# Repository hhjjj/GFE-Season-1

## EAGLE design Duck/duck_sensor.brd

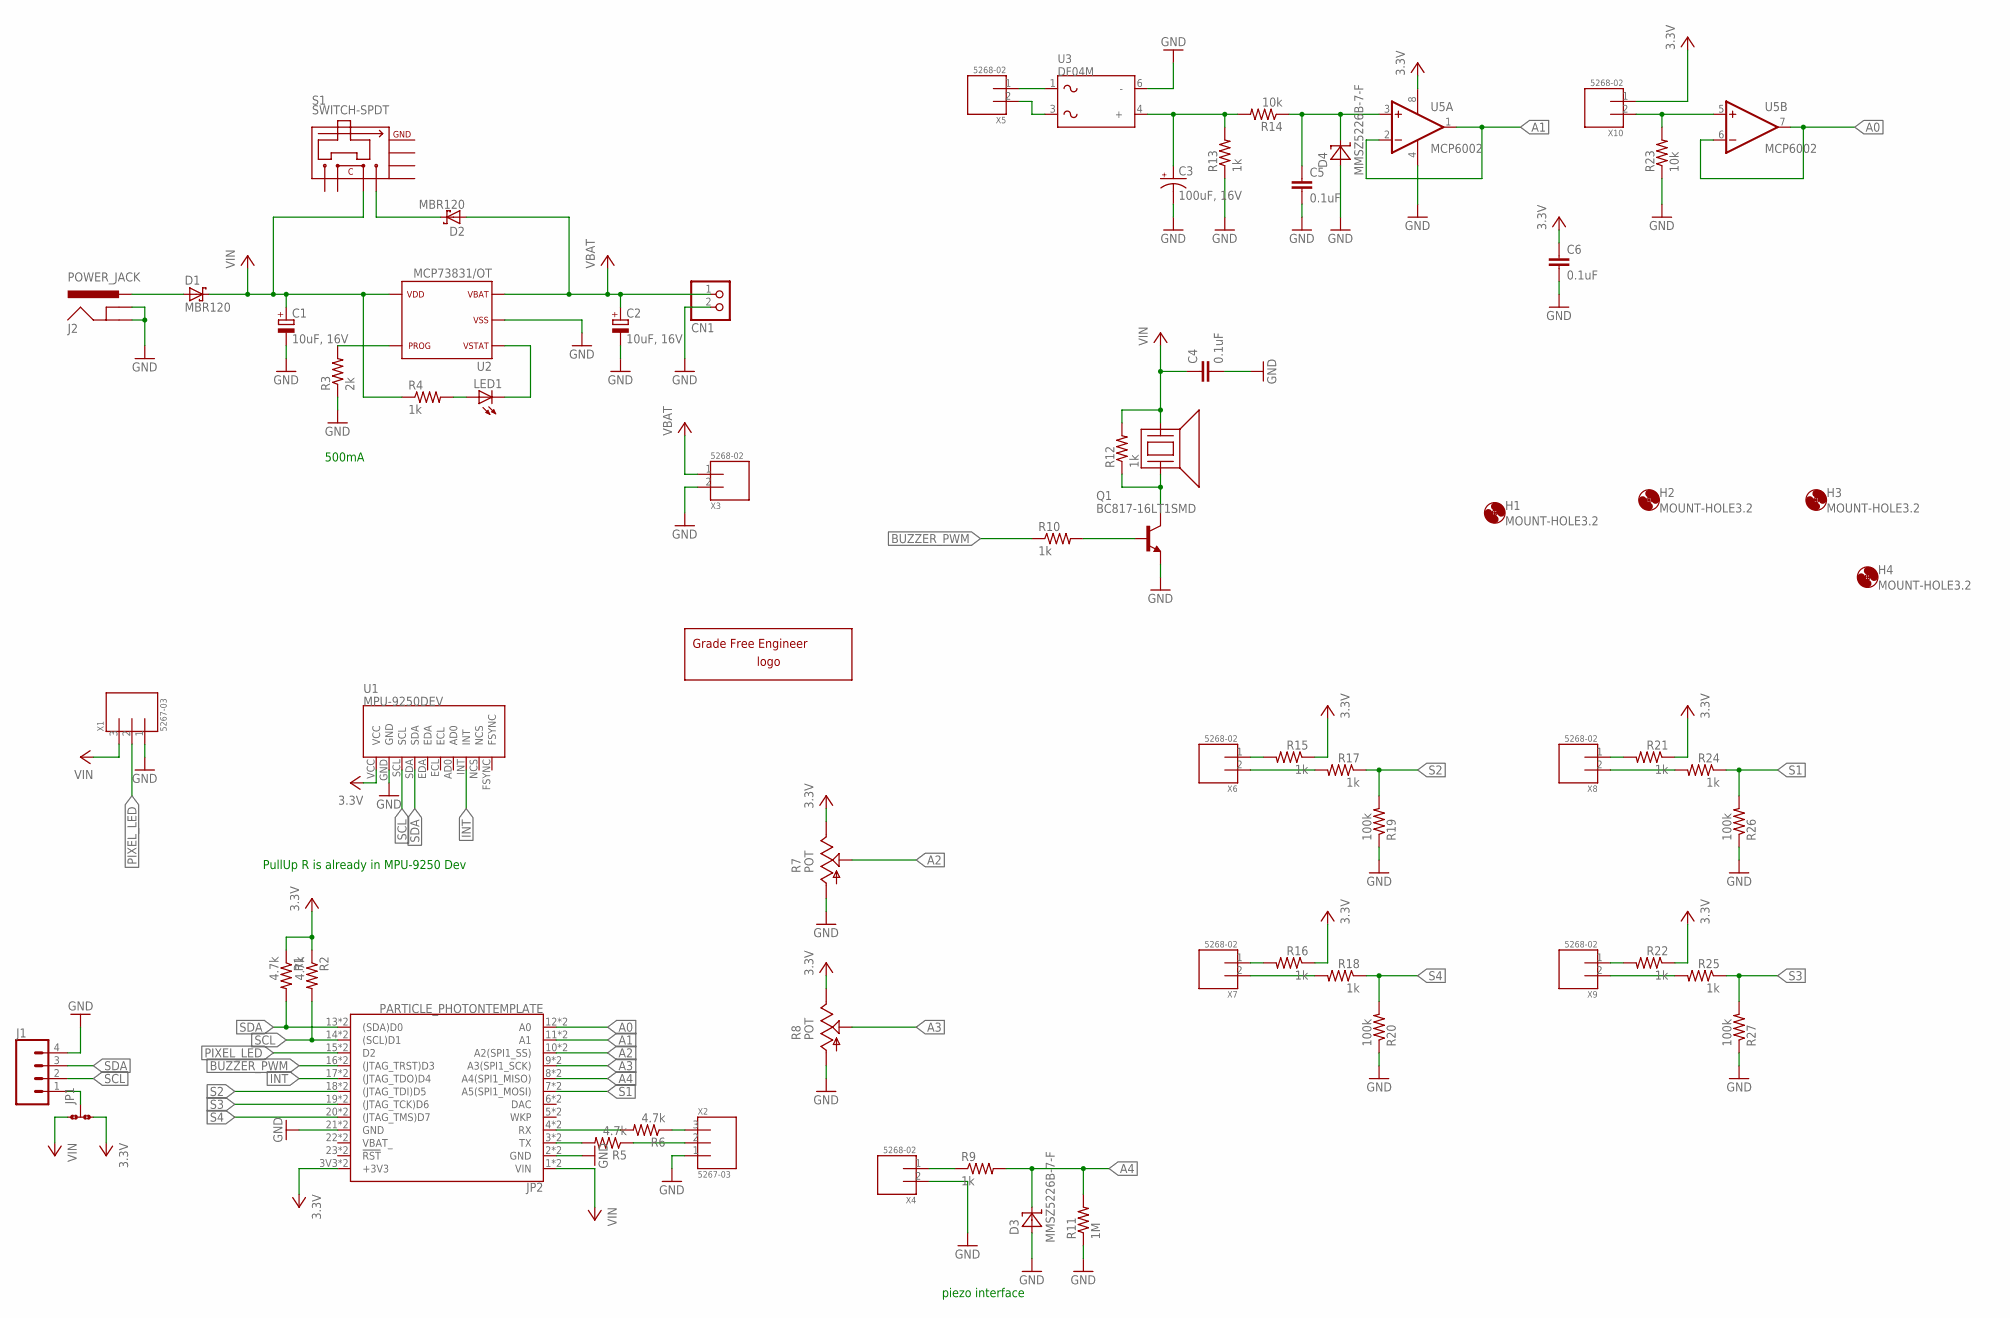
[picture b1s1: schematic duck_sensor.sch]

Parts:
C1, C2: 10uF, 16V; C1206(3216)-A
C3: 100uF, 16V; E2,5-6E
C4, C5, C6: 0.1uF; C0603(1608)_HANDSOLDER
CN1: JST_2PIN-SMT-RA; JST-PH-2-SMT-RA
D1, D2: MBR120; SOD-123
D3, D4: MMSZ5226B-7-F; SOD-123
H1, H2, H3, H4: MOUNT-HOLE3.2; 3,2
J1: CONN_04; 1X04
J2: POWER_JACK; POWER_JACK_PTH
JP1: JP2; JP2SMD0603
JP2: PARTICLE_PHOTONTEMPLATE; PARTICLE_PHOTON_TEMPLATE
LED1: LED0603; LED-0603
LOGO1: GRADEFREELOGO-20
Q1: BC817-16LT1SMD; SOT23-BEC
R1, R2, R5, R6: 4.7k; R0603(1608)_HANDSOLDER
R3: 2k; R0603(1608)_HANDSOLDER
R4, R9, R10, R12, R13, R15, R16, R17, R18, R21, R22, R24, R25: 1k; R0603(1608)_HANDSOLDER
R7, R8: POT; RK09L
R11: 1M; R0603(1608)_HANDSOLDER
R14, R23: 10k; R0603(1608)_HANDSOLDER
R19, R20, R26, R27: 100k; R0603(1608)_HANDSOLDER
S1: SWITCH-SPDT; SSSS810201
U1: MPU-9250DEV; MPU-9250
U2: MCP73831/OT; SOT23-5L
U3: DF04M; DIL06
U4: BUZZER; PS1240
U5: MCP6002; DIL08
X1, X2: 5267-03
X3, X4, X5, X6, X7, X8, X9, X10: 5268-02; 5628-02

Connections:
3.3V: C6.1, JP1.3, JP2.3V3 (+3V3), JP2.24 (+3V3), R1.1, R2.1, R7.1 (E), R8.1 (E), R15.1, R16.1, R21.1, R22.1, U1.VCC, U5.8 (V+), X10.1
A0: JP2.12 (A0), JP2.A0, U5.6 (-IN), U5.7 (OUT)
A1: JP2.11 (A1), JP2.A1, U5.1 (OUT), U5.2 (-IN)
A2: JP2.10 (A2(SPI1_SS)), JP2.A2 (A2(SPI1_SS)), R7.2 (S)
A3: JP2.9 (A3(SPI1_SCK)), JP2.A3 (A3(SPI1_SCK)), R8.2 (S)
A4: D3.C, JP2.8 (A4(SPI1_MISO)), JP2.A4 (A4(SPI1_MISO)), R9.2, R11.2
BUZZER_PWM: JP2.16 ((JTAG_TRST)D3), JP2.D3 ((JTAG_TRST)D3), R10.1
GND: C1.2 (-), C2.2 (-), C3.-, C4.2, C5.2, C6.2, CN1.2 (1), D3.A, D4.A, J1.4, J2.GND, J2.GNDBREAK, JP2.2 (GND), JP2.21 (GND), JP2.GND@0 (GND), JP2.GND@2 (GND), Q1.E, R3.1, R7.3 (A), R8.3 (A), R11.1, R13.1, R19.1, R20.1, R23.1, R26.1, R27.1, U1.GND, U2.2 (VSS), U3.6 (-), U5.4 (V-), X1.1, X2.1, X3.2, X4.2
INT: JP2.17 ((JTAG_TDO)D4), JP2.D4 ((JTAG_TDO)D4), U1.INT
unnamed: D2.C, S1.1
unnamed: R15.2, X6.1
unnamed: LED1.A, R4.2
unnamed: LED1.C, U2.1 (STAT)
unnamed: R3.2, U2.5 (PROG)
unnamed: D1.A, J2.PWR
unnamed: R9.1, X4.1
unnamed: R17.2, X6.2
unnamed: R16.2, X7.1
unnamed: R18.2, X7.2
unnamed: JP2.3 (TX), JP2.TX, R5.2
unnamed: JP2.4 (RX), JP2.RX, R6.2
unnamed: R6.1, X2.3
unnamed: R5.1, X2.2
unnamed: Q1.B, R10.2
unnamed: Q1.C, R12.1, U4.2
unnamed: J1.1, JP1.2
unnamed: C5.1, D4.C, R14.1, U5.3 (+IN)
unnamed: R23.2, U5.5 (+IN), X10.2
unnamed: R21.2, X8.1
unnamed: R24.2, X8.2
unnamed: R22.2, X9.1
unnamed: C3.+, R13.2, R14.2, U3.4 (+)
unnamed: U3.1, X5.1
unnamed: U3.3, X5.2
unnamed: R25.2, X9.2
PIXEL_LED: JP2.15 (D2), JP2.D2, X1.2
S1: JP2.7 (A5(SPI1_MOSI)), JP2.A5 (A5(SPI1_MOSI)), R24.1, R26.2
S2: JP2.18 ((JTAG_TDI)D5), JP2.D5 ((JTAG_TDI)D5), R17.1, R19.2
S3: JP2.19 ((JTAG_TCK)D6), JP2.D6 ((JTAG_TCK)D6), R25.1, R27.2
S4: JP2.20 ((JTAG_TMS)D7), JP2.D7 ((JTAG_TMS)D7), R18.1, R20.2
SCL: J1.2, JP2.14 ((SCL)D1), JP2.D1 ((SCL)D1), R2.2, U1.SCL
SDA: J1.3, JP2.13 ((SDA)D0), JP2.D0 ((SDA)D0), R1.2, U1.SDA
VBAT: C2.1 (+), CN1.1 (2), D2.A, U2.3 (VBAT), X3.1
VBAT_: JP2.22 (VBAT_), JP2.VBAT_
VIN: C1.1 (+), C4.1, D1.C, JP1.1, JP2.1 (VIN), JP2.VIN, R4.1, R12.2, S1.2, U2.4 (VDD), U4.1, X1.3

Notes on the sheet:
500mA
PullUp R is already in MPU-9250 Dev
piezo interface

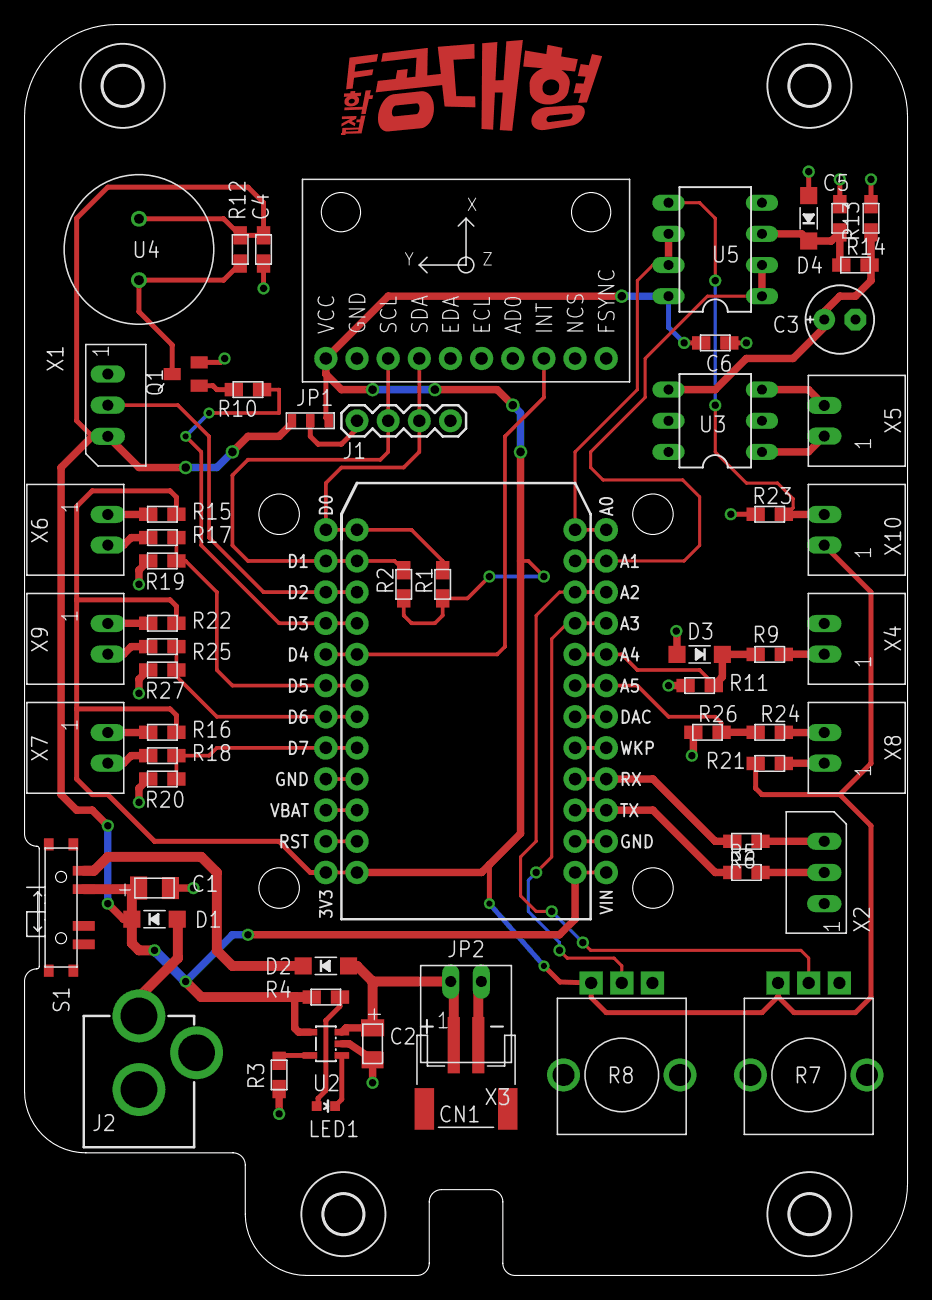
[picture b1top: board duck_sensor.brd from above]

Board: 2 copper layers, 72.0 x 102.0 mm, 65 parts (0 on the bottom side), 45 nets.

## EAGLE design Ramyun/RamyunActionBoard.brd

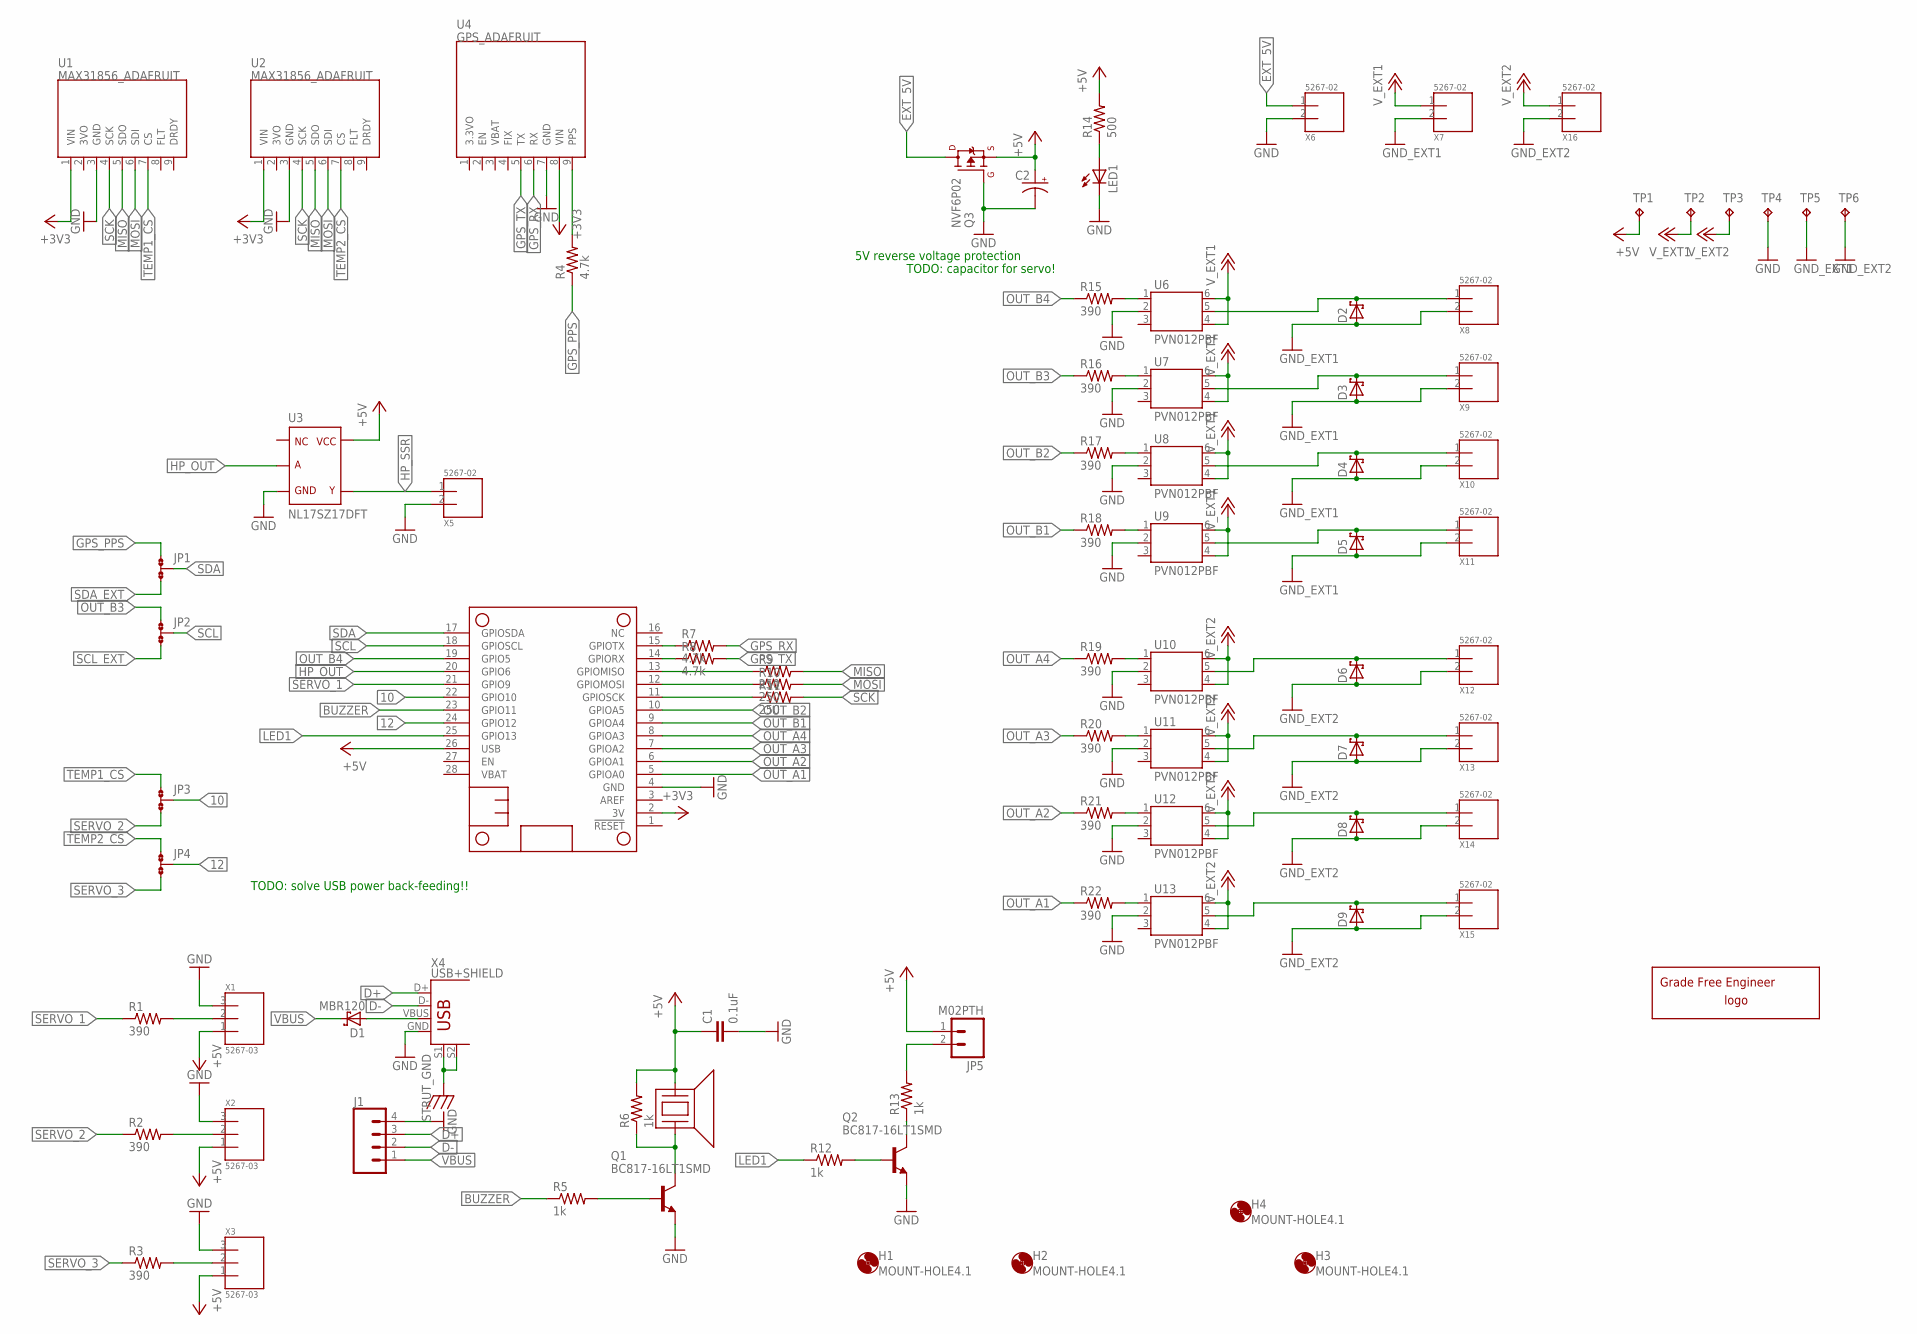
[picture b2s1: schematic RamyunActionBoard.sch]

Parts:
C1: 0.1uF; C0603(1608)_HANDSOLDER
C2: CPOL-USE3.5-8; E3,5-8
D1: MBR120; SOD-123
D2, D3, D4, D5, D6, D7, D8, D9: MBR5200VPTR-E1_V; DO-27-VERTICAL
H1, H2, H3, H4: MOUNT-HOLE4.1; 4,1
J1: CONN_04; 1X04
JP1, JP2, JP3, JP4: JP2; JP2SMD0603
JP5: M02PTH; 1X02
LED1: LED3MM
LOGO1: GRADEFREELOGO-20
MS1: FEATHERWING_NODIM; FEATHERWING_DIM
Q1, Q2: BC817-16LT1SMD; SOT23-BEC
Q3: NVF6P02; SOT223
R1, R2, R3, R15, R16, R17, R18, R19, R20, R21, R22: 390; R0603(1608)_HANDSOLDER
R4, R7, R8: 4.7k; R0603(1608)_HANDSOLDER
R5, R6, R12, R13: 1k; R0603(1608)_HANDSOLDER
R9, R10, R11: 250; R0603(1608)_HANDSOLDER
R14: 500; R0603(1608)_HANDSOLDER
TP1, TP2, TP3, TP4, TP5, TP6: TP-5010
U1, U2: MAX31856_ADAFRUIT
U3: NL17SZ17DFT; SOT-353
U4: GPS_ADAFRUIT
U5: BUZZER; PS1240
U6, U7, U8, U9, U10, U11, U12, U13: PVN012PBF; DIL06
X1, X2, X3: 5267-03
X4: USB+SHIELD; USB-B-PTH
X5, X6, X7, X8, X9, X10, X11, X12, X13, X14, X15, X16: 5267-02

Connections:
10: JP3.2, MS1.22 (GPIO10)
12: JP4.2, MS1.24 (GPIO12)
+3V3: MS1.2 (3V), U1.1 (VIN), U2.1 (VIN), U4.8 (VIN)
+5V: C1.1, C2.+, JP5.1, MS1.26 (USB), Q3.3 (S), R6.2, R14.2, TP1.TP, U3.5, U5.1, X1.1, X2.1, X3.1
BUZZER: MS1.23 (GPIO11), R5.1
D+: J1.3, X4.D+
D-: J1.2, X4.D-
EXT_5V: Q3.2 (D), Q3.4 (D), X6.1
GND: C1.2, C2.-, J1.4, LED1.K (C), MS1.4 (GND), Q1.E, Q2.E, Q3.1 (G), TP4.TP, U1.3 (GND), U2.3 (GND), U3.3, U4.7 (GND), U6.2, U7.2, U8.2, U9.2, U10.2, U11.2, U12.2, U13.2, X1.3, X2.3, X3.3, X4.GND, X5.2, X6.2
GND_EXT1: D2.A, D3.A, D4.A, D5.A, TP5.TP, X7.2, X8.2, X9.2, X10.2, X11.2
GND_EXT2: D6.A, D7.A, D8.A, D9.A, TP6.TP, X12.2, X13.2, X14.2, X15.2, X16.2
GPS_PPS: JP1.1, R4.1
GPS_RX: R7.2, U4.6 (RX)
GPS_TX: R8.2, U4.5 (TX)
HP_OUT: MS1.20 (GPIO6), U3.2
HP_SSR: U3.4, X5.1
LED1: MS1.25 (GPIO13), R12.1
MISO: R9.2, U1.5 (SDO), U2.5 (SDO)
MOSI: R10.2, U1.6 (SDI), U2.6 (SDI)
unnamed: R22.2, U13.1
unnamed: R21.2, U12.1
unnamed: R20.2, U11.1
unnamed: R19.2, U10.1
unnamed: R18.2, U9.1
unnamed: R17.2, U8.1
unnamed: R16.2, U7.1
unnamed: R15.2, U6.1
unnamed: R1.2, X1.2
unnamed: R2.2, X2.2
unnamed: R3.2, X3.2
unnamed: D1.A, X4.VBUS
unnamed: JP5.2, R13.2
unnamed: Q2.C, R13.1
unnamed: Q2.B, R12.2
unnamed: LED1.A, R14.1
unnamed: Q1.B, R5.2
unnamed: Q1.C, R6.1, U5.2
unnamed: MS1.15 (GPIOTX), R7.1
unnamed: MS1.14 (GPIORX), R8.1
unnamed: MS1.13 (GPIOMISO), R9.1
unnamed: MS1.12 (GPIOMOSI), R10.1
unnamed: D2.C, U6.5, X8.1
unnamed: D3.C, U7.5, X9.1
unnamed: D4.C, U8.5, X10.1
unnamed: D5.C, U9.5, X11.1
unnamed: D6.C, U10.5, X12.1
unnamed: D7.C, U11.5, X13.1
unnamed: D8.C, U12.5, X14.1
unnamed: D9.C, U13.5, X15.1
unnamed: MS1.11 (GPIOSCK), R11.1
unnamed: R4.2, U4.9 (PPS)
OUT_A1: MS1.5 (GPIOA0), R22.1
OUT_A2: MS1.6 (GPIOA1), R21.1
OUT_A3: MS1.7 (GPIOA2), R20.1
OUT_A4: MS1.8 (GPIOA3), R19.1
OUT_B1: MS1.9 (GPIOA4), R18.1
OUT_B2: MS1.10 (GPIOA5), R17.1
OUT_B3: JP2.1, R16.1
OUT_B4: MS1.19 (GPIO5), R15.1
SCK: R11.2, U1.4 (SCK), U2.4 (SCK)
SCL: JP2.2, MS1.18 (GPIOSCL)
SCL_EXT: JP2.3
SDA: JP1.2, MS1.17 (GPIOSDA)
SDA_EXT: JP1.3
SERVO_1: MS1.21 (GPIO9), R1.1
SERVO_2: JP3.3, R2.1
SERVO_3: JP4.3, R3.1
STRUT_GND: X4.S1, X4.S2
TEMP1_CS: JP3.1, U1.7 (CS)
TEMP2_CS: JP4.1, U2.7 (CS)
VBUS: D1.C, J1.1
V_EXT1: TP2.TP, U6.4, U6.6, U7.4, U7.6, U8.4, U8.6, U9.4, U9.6, X7.1
V_EXT2: TP3.TP, U10.4, U10.6, U11.4, U11.6, U12.4, U12.6, U13.4, U13.6, X16.1

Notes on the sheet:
TODO: capacitor for servo!
5V reverse voltage protection
TODO: solve USB power back-feeding!!

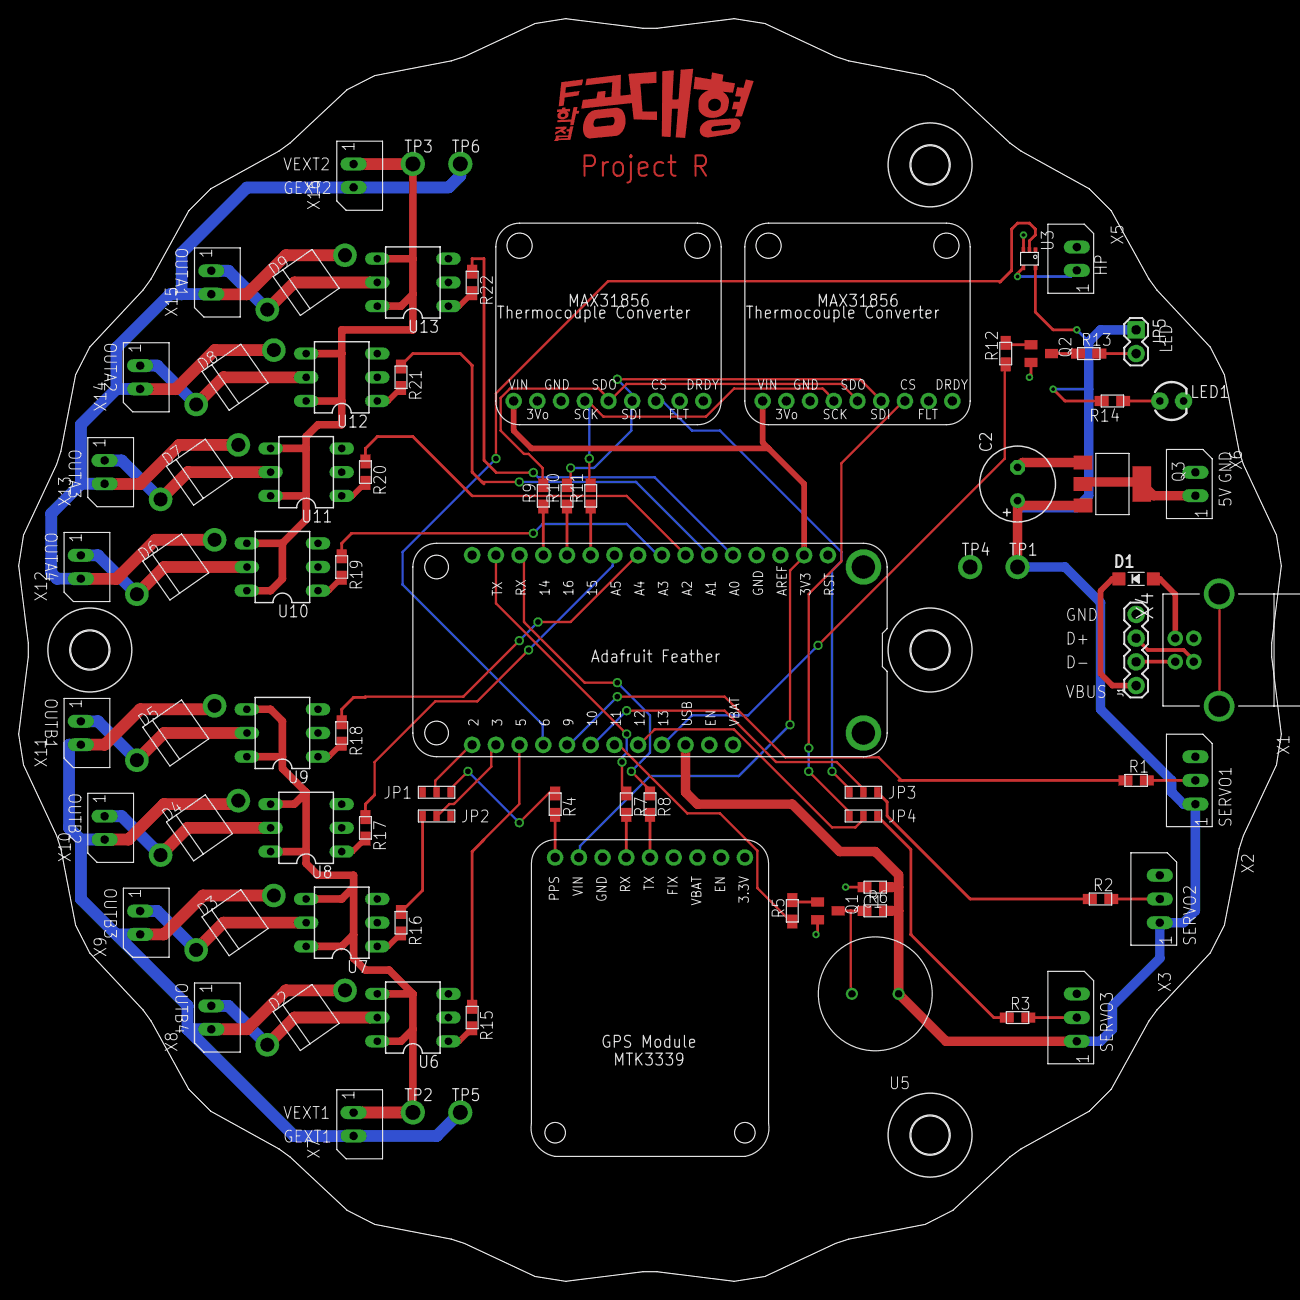
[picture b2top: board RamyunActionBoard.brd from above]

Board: 2 copper layers, 135.2 x 135.2 mm, 84 parts (0 on the bottom side), 71 nets.

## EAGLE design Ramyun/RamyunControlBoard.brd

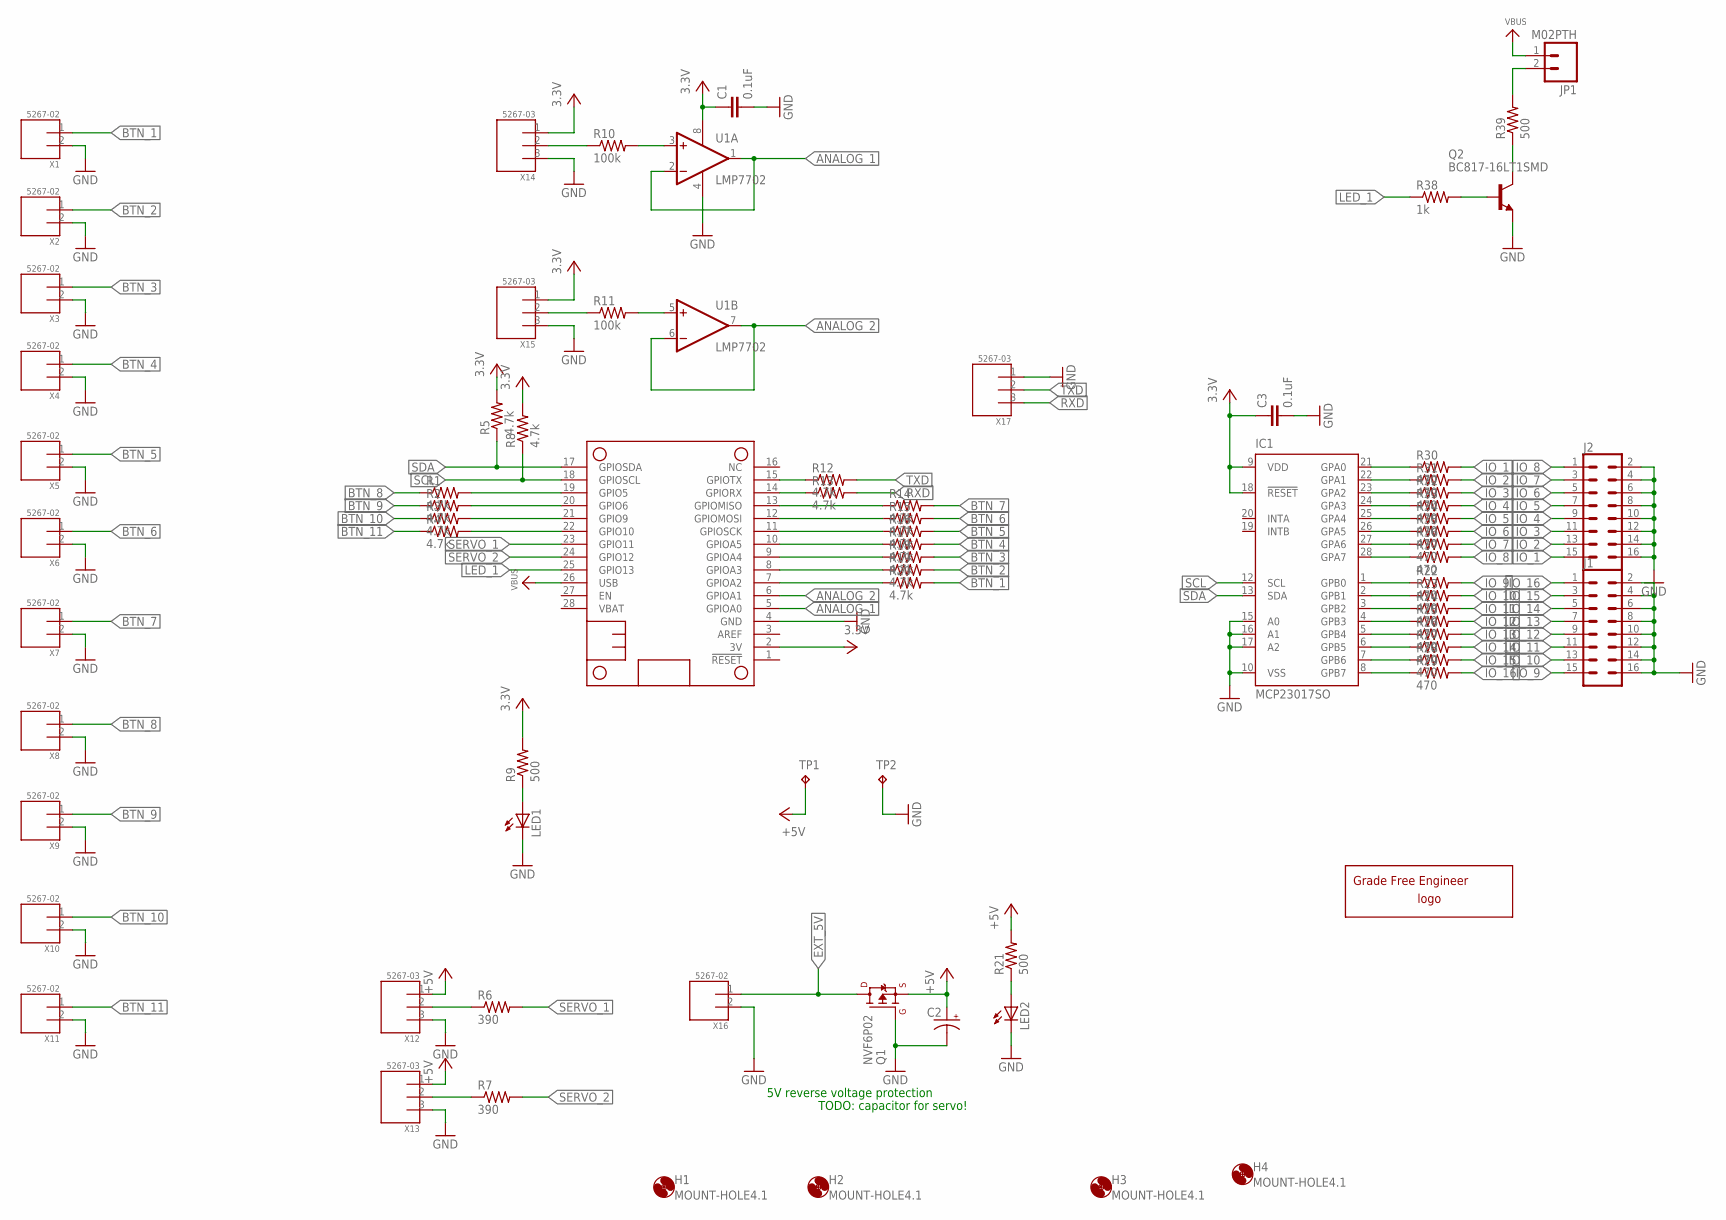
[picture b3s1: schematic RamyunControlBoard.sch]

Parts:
C1, C3: 0.1uF; C0603(1608)_HANDSOLDER
C2: CPOL-USE3.5-8; E3,5-8
H1, H2, H3, H4: MOUNT-HOLE4.1; 4,1
IC1: MCP23017SO; SO28W
J1, J2: CONN_08X2; 2X8
JP1: M02PTH; 1X02
LED1, LED2: LED3MM
LOGO1: GRADEFREELOGO-20
MS1: FEATHERWING_NODIM; FEATHERWING_DIM
Q1: NVF6P02; SOT223
Q2: BC817-16LT1SMD; SOT23-BEC
R1, R2, R3, R4, R5, R8, R12, R13, R14, R15, R16, R17, R18, R19, R20: 4.7k; R0603(1608)_HANDSOLDER
R6, R7: 390; R0603(1608)_HANDSOLDER
R9, R21, R39: 500; R0603(1608)_HANDSOLDER
R10, R11: 100k; R0603(1608)_HANDSOLDER
R22, R23, R24, R25, R26, R27, R28, R29, R30, R31, R32, R33, R34, R35, R36, R37: 470; R0603(1608)_HANDSOLDER
R38: 1k; R0603(1608)_HANDSOLDER
TP1, TP2: TP-5010
U1: LMP7702; DGK_S-DPSO-G8
X1, X2, X3, X4, X5, X6, X7, X8, X9, X10, X11, X16: 5267-02
X12, X13, X14, X15, X17: 5267-03

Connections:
3.3V: C1.1, C3.1, IC1.9 (VDD), IC1.18 (!RESET), MS1.2 (3V), R5.2, R8.2, R9.2, U1.8 (V+), X14.1, X15.1
+5V: C2.+, Q1.3 (S), R21.2, TP1.TP, X12.1, X13.1
ANALOG_1: MS1.5 (GPIOA0), U1.1 (OUT), U1.2 (-IN)
ANALOG_2: MS1.6 (GPIOA1), U1.6 (-IN), U1.7 (OUT)
BTN_1: R20.2, X1.1
BTN_2: R19.2, X2.1
BTN_3: R18.2, X3.1
BTN_4: R17.2, X4.1
BTN_5: R16.2, X5.1
BTN_6: R15.2, X6.1
BTN_7: R14.2, X7.1
BTN_8: R1.1, X8.1
BTN_9: R2.1, X9.1
BTN_10: R3.1, X10.1
BTN_11: R4.1, X11.1
EXT_5V: Q1.2 (D), Q1.4 (D), X16.1
GND: C1.2, C2.-, C3.2, IC1.10 (VSS), IC1.15 (A0), IC1.16 (A1), IC1.17 (A2), J1.2, J1.4, J1.6, J1.8, J1.10, J1.12, J1.14, J1.16, J2.2, J2.4, J2.6, J2.8, J2.10, J2.12, J2.14, J2.16, LED1.K (C), LED2.K (C), MS1.4 (GND), Q1.1 (G), Q2.E, TP2.TP, U1.4 (V-), X1.2, X2.2, X3.2, X4.2, X5.2, X6.2, X7.2, X8.2, X9.2, X10.2, X11.2, X12.3, X13.3, X14.3, X15.3, X16.2, X17.1
IO_1: J2.15, R30.2
IO_2: J2.13, R31.2
IO_3: J2.11, R32.2
IO_4: J2.9, R33.2
IO_5: J2.7, R34.2
IO_6: J2.5, R35.2
IO_7: J2.3, R36.2
IO_8: J2.1, R37.2
IO_9: J1.15, R22.2
IO_10: J1.13, R23.2
IO_11: J1.11, R24.2
IO_12: J1.9, R25.2
IO_13: J1.7, R26.2
IO_14: J1.5, R27.2
IO_15: J1.3, R28.2
IO_16: J1.1, R29.2
LED_1: MS1.25 (GPIO13), R38.1
unnamed: MS1.7 (GPIOA2), R20.1
unnamed: R10.2, U1.3 (+IN)
unnamed: R11.2, U1.5 (+IN)
unnamed: MS1.8 (GPIOA3), R19.1
unnamed: MS1.9 (GPIOA4), R18.1
unnamed: MS1.10 (GPIOA5), R17.1
unnamed: R11.1, X15.2
unnamed: R10.1, X14.2
unnamed: MS1.19 (GPIO5), R1.2
unnamed: MS1.20 (GPIO6), R2.2
unnamed: MS1.21 (GPIO9), R3.2
unnamed: MS1.22 (GPIO10), R4.2
unnamed: MS1.15 (GPIOTX), R12.1
unnamed: MS1.14 (GPIORX), R13.1
unnamed: MS1.11 (GPIOSCK), R16.1
unnamed: MS1.12 (GPIOMOSI), R15.1
unnamed: MS1.13 (GPIOMISO), R14.1
unnamed: IC1.21 (GPA0), R30.1
unnamed: IC1.22 (GPA1), R31.1
unnamed: IC1.23 (GPA2), R32.1
unnamed: IC1.24 (GPA3), R33.1
unnamed: IC1.25 (GPA4), R34.1
unnamed: IC1.26 (GPA5), R35.1
unnamed: IC1.27 (GPA6), R36.1
unnamed: IC1.28 (GPA7), R37.1
unnamed: IC1.1 (GPB0), R22.1
unnamed: IC1.2 (GPB1), R23.1
unnamed: IC1.3 (GPB2), R24.1
unnamed: IC1.4 (GPB3), R25.1
unnamed: IC1.5 (GPB4), R26.1
unnamed: IC1.6 (GPB5), R27.1
unnamed: IC1.7 (GPB6), R28.1
unnamed: IC1.8 (GPB7), R29.1
unnamed: R6.1, X12.2
unnamed: R7.1, X13.2
unnamed: LED2.A, R21.1
unnamed: Q2.C, R39.1
unnamed: Q2.B, R38.2
unnamed: JP1.2, R39.2
unnamed: LED1.A, R9.1
RXD: R13.2, X17.3
SCL: IC1.12 (SCL), MS1.18 (GPIOSCL), R8.1
SDA: IC1.13 (SDA), MS1.17 (GPIOSDA), R5.1
SERVO_1: MS1.23 (GPIO11), R6.2
SERVO_2: MS1.24 (GPIO12), R7.2
TXD: R12.2, X17.2
VBUS: JP1.1, MS1.26 (USB)

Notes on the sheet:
TODO: capacitor for servo!
5V reverse voltage protection

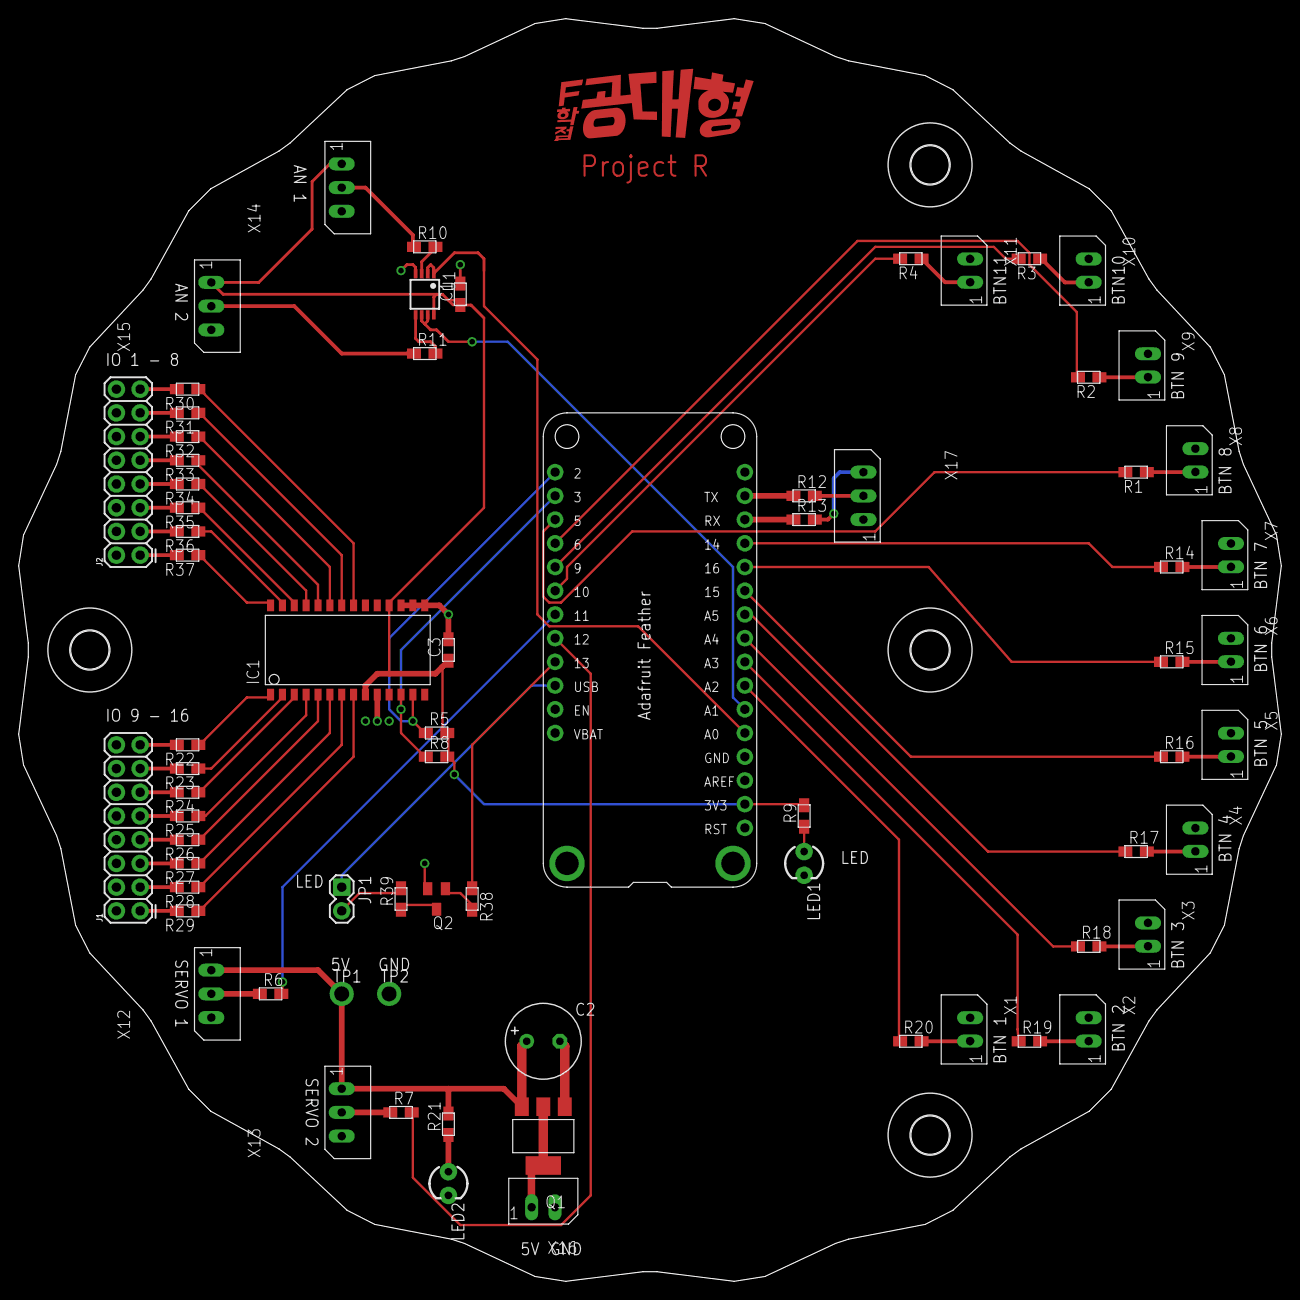
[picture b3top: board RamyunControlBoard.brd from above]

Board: 2 copper layers, 135.2 x 135.2 mm, 76 parts (0 on the bottom side), 81 nets.

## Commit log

2017-01-22 first
2017-01-22 folder change
2017-01-23 outline
2017-01-24 layout almost done
2017-01-24 tired
2017-01-24 tired 2
2017-01-25 gerber done
2017-01-27 nl17sz17
    package added
2017-01-29 value changed
2017-04-20 duck
2017-04-21 gerber
2017-04-21 comment
2017-04-22 comment added

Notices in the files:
parts and their libraries:
SparkFun-Connectors: Licensing: Creative Commons ShareAlike 4.0 International - https://creativecommons.org/licenses/by-sa/4.0
